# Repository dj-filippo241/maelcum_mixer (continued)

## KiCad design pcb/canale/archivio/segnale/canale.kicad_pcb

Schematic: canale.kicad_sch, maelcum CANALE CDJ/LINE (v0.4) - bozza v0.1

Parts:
C1, C2: 220u 35V; CP_Radial_D8.0mm_P3.50mm
C3: 47u 10V; CP_Radial_D5.0mm_P2.00mm
C4, C8: 10u 35V; CP_Radial_D5.0mm_P2.00mm
C5, C9: 47u 35V; CP_Radial_D6.3mm_P2.50mm
C6, C10: 470u 25V; CP_Radial_D8.0mm_P3.50mm
C7, C11: 100u 25V; CP_Radial_D6.3mm_P2.50mm
C12, C13: 1u 50V; C_1206_3216Metric
C14, C15: 1u 25V; C_1206_3216Metric
C16, C17, C19, C20: 4u7 25V; C_1206_3216Metric
C18, C21: 10u 25V; C_1206_3216Metric
C22: 1u; C_1206_3216Metric
C23, C24, C27, C28, C29, C30, C31, C32, C33, C34, C37, C38, C39, C40, C42, C43, C45, C46, C47, C48, C51, C52, C53, C54, C55, C56, C57, C59, C60, C61, C62, C63: 100n; C_0805_2012Metric
C25, C26: 2u2 film; C_1812_4532Metric
C35: 47p C0G; C_0805_2012Metric
C36: 100n C0G; C_1206_3216Metric
C41, C44: 22p C0G; C_0805_2012Metric
C49, C50: 50n C0G; C_1206_3216Metric
C58: 47n; C_0805_2012Metric
D1, D3, D8, D9, D10, D11, D12, D13: 1N4148W; D_SOD-123
D2, D4: S1G; D_SMA
D5: LM4040-5.0; SOT-23
D6, D7: TVS bidir <=5 pF; D_SOD-323
FB1, FB2, FB3, FB4, FB5, FB6, FB7: ferrite 600R; L_1206_3216Metric
H1, H2: CHASSIS; MountingHole_3.2mm_M3_Pad
J1: C96 maschio; DIN41612_C_3x32_Male_Horizontal_THT
J2: 2x18 cavo piatto; PinHeader_2x18_P2.54mm_Vertical
J3: 1x5 ingressi; PinHeader_1x05_P2.54mm_Vertical
J4: 2x18 ponte isolator; PinHeader_2x18_P2.54mm_Vertical
Q40: BD139; TO-126-3_Vertical
Q41: BD140; TO-126-3_Vertical
R1, R4: 120 1%; R_0805_2012Metric
R2, R5: 1k74 1%; R_0805_2012Metric
R3, R6, R29, R67, R68: 1k; R_0805_2012Metric
R7, R8: 150k 0.1%; R_0805_2012Metric
R9: 1k5; R_0805_2012Metric
R10, R11, R48, R49, R71, R72, R73, R74, R75, R76: 10k 0.1%; R_0805_2012Metric
R12, R17: 100; R_0805_2012Metric
R13, R18, R51, R65, R70: 100k; R_0805_2012Metric
R14, R19: 4k30 0.1%; R_0805_2012Metric
R15, R20: 2k15 0.1%; R_0805_2012Metric
R16, R21, R52: 1k 0.1%; R_0805_2012Metric
R22, R23, R24, R25: 47; R_0805_2012Metric
R26, R27, R31, R35, R36, R40: 20k 0.1%; R_0805_2012Metric
R28: 4k02 0.1%; R_0805_2012Metric
R30: 3M; R_0805_2012Metric
R32, R37: 6k19; R_0805_2012Metric
R33, R38: 150k; R_0805_2012Metric
R34, R39: 51; R_0805_2012Metric
R41: 43.2k 0.1%; R_0805_2012Metric
R42: 68.1k 0.1%; R_0805_2012Metric
R43: 357k 0.1%; R_0805_2012Metric
R44: 20.0k 0.1%; R_0805_2012Metric
R45: 38.3k 0.1%; R_0805_2012Metric
R46: 976 0.1%; R_0805_2012Metric
R47: 1.33k 0.1%; R_0805_2012Metric
R50: 2k 0.1%; R_0805_2012Metric
R53, R55: 1k5 0.1%; R_0805_2012Metric
R54: 909 0.1%; R_0805_2012Metric
R56: 1M5; R_0805_2012Metric
R57, R58, R61, R62, R63, R64, R69: 10k; R_0805_2012Metric
R59, R60: 3k01 0.1%; R_0805_2012Metric
R66: 33k; R_0805_2012Metric
RV1, RV2, RV4: 50k; Potentiometer_Bourns_3266W_Vertical
RV3: 200; Potentiometer_Bourns_3266W_Vertical
U1, U2, U15, U16, U20, U21, U22, U46: OPA1612AIDR; SOIC-8_3.9x4.9mm_P1.27mm
U17: OPA1654AIDR; SOIC-14_3.9x8.7mm_P1.27mm
U18, U19: V2181L; SOIC-8_3.9x4.9mm_P1.27mm
U23: 74HC14PW; TSSOP-14_4.4x5mm_P0.65mm
U24: 74HC86PW; TSSOP-14_4.4x5mm_P0.65mm
U25: 74HC74PW; TSSOP-14_4.4x5mm_P0.65mm
U26, U27: ADG1434YRUZ; TSSOP-20_4.4x6.5mm_P0.65mm
U40: LM317; TO-220-3_Vertical
U41: LM337; TO-220-3_Vertical
U42: 78L15; SOT-89-3
U43: 79L15; SOT-89-3
U44: LT3045EMSE; MSOP-12-1EP_3x4.039mm_P0.65mm_EP1.651x2.845mm
U45: LT3094EMSE; MSOP-12-1EP_3x4.039mm_P0.65mm_EP1.651x2.845mm

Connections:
+5V: FB5.1, J1.a21, J1.a22
+5VF: C3.1, C55.1, C56.1, C57.1, FB5.2, J2.33, R61.1, R63.1, U23.14 (VCC), U24.14 (VCC), U25.1 (1CLR), U25.4 (1PRE), U25.10 (2PRE), U25.13 (2CLR), U25.14 (VCC)
+15LN: C18.1, C23.1, C47.1, C51.1, R9.1, RV1.1, RV2.1, RV4.1, U21.8 (V+), U22.8 (V+), U44.10 (OUTS), U44.11 (OUT), U44.12 (OUT), U46.8 (V+)
+15SW: C14.1, C60.1, C62.1, U26.16 (VDD), U27.16 (VDD), U42.1 (OUT)
+18V: C7.1, C17.1, C27.1, C29.1, C31.1, C33.1, C37.1, C39.1, C42.1, C45.1, J4.1, J4.2, Q40.1 (E), U1.8 (V+), U2.8 (V+), U15.8 (V+), U16.8 (V+), U17.4 (V+), U18.7 (V+), U19.7 (V+), U20.8 (V+), U44.1 (IN), U44.2 (IN), U44.3 (IN), U44.4 (EN/UV), U44.7 (PGFB)
+REF5: J2.26, R10.1, U46.1, U46.2 (-)
-15LN: C21.2, C24.2, C48.2, C52.2, RV1.3, RV2.3, RV4.3, U21.4 (V-), U22.4 (V-), U45.10 (OUTS), U45.11 (OUT), U45.12 (OUT), U46.4 (V-)
-15SW: C15.2, C61.2, C63.2, U26.5 (VSS), U27.5 (VSS), U43.3 (VO)
-18V: C11.2, C20.2, C28.2, C30.2, C32.2, C34.2, C38.2, C40.2, C43.2, C46.2, J4.5, J4.6, Q41.1 (E), R32.2, R37.2, U1.4 (V-), U2.4 (V-), U15.4 (V-), U16.4 (V-), U17.11 (V-), U20.4 (V-), U45.1 (IN), U45.2 (IN), U45.3 (EN/UV), U45.5 (PGFB), U45.13 (IN)
-REF5: R11.2, R43.2, R45.2, R47.2, U46.7
ADJ+: C4.1, D1.2 (A), R1.2, R2.1, U40.1 (ADJ)
ADJ-: C8.2, D3.1 (K), R4.2, R5.1, U41.1 (ADJ)
AGND: C1.2, C2.1, C4.2, C5.2, C6.2, C7.2, C8.1, C9.1, C10.1, C11.1, C12.2, C13.1, C14.2, C15.1, C16.2, C17.2, C18.2, C19.1, C20.1, C21.1, C22.2, C23.2, C24.1, C27.2, C28.1, C29.2, C30.1, C31.2, C32.1, C33.2, C34.1, C36.2, C37.2, C38.1, C39.2, C40.1, C42.2, C43.1, C45.2, C46.1, C47.2, C48.1, C49.2, C50.2, C51.2, C52.1, C60.2, C61.1, C62.2, C63.1, D5.2 (A), D6.2 (A2), D7.2 (A2), J1.a13, J1.a14, J1.a15, J1.a16, J1.a17, J1.a18, J1.a19, J1.a20, J1.b3, J1.b6, J1.b9, J1.b12, J1.b15, J1.b18, J1.b21, J1.b24, J1.b27, J1.b30, J2.1, J2.4, J2.7, J2.16, J2.25, J2.28, J2.35, J2.36, J3.2, J3.4, J4.3, J4.4, J4.7, J4.8, J4.11, J4.12, J4.15, J4.16, J4.25, J4.26, J4.35, J4.36, R2.2, R5.2, R7.2, R8.2, R13.2, R14.2, R16.2, R18.2, R19.2, R21.2, R28.2, R30.2, R34.2, R39.2, R51.2, R53.2, R55.2, U17.12 (+), U18.2 (EC+), U18.6 (GND), U19.2 (EC+), U19.6 (GND), U20.3 (+), U20.5 (+), U21.3 (+), U21.5 (+), U26.4 (S1B), U26.6 (GND), U26.7 (S2B), U26.14 (S3B), U26.17 (S4B), U27.4 (S1B), U27.6 (GND), U27.7 (S2B), U27.14 (S3B), U27.17 (S4B), U42.2 (GND), U43.1 (GND), U44.6 (ILIM), U44.9 (GND), U44.13 (GND), U45.6 (ILIM), U45.9 (GND), U46.5 (+)
BASE+: C6.1, Q40.3 (B), R3.2
BASE-: C10.2, Q41.3 (B), R6.2
BTNC: J2.32, R69.1
BUF_L: J2.2, U1.1, U1.2 (-)
BUF_R: J2.5, U1.6 (-), U1.7
BUS_HPF_L: J1.b10, R72.2
BUS_HPF_R: J1.b11, R75.2
BUS_LPF_L: J1.b13, R73.2
BUS_LPF_R: J1.b14, R76.2
CHASSIS: H1.1, H2.1, J1.a25, J1.a26, J3.5
CLK: U23.8 (4Y), U25.3 (1CLK), U25.11 (2CLK)
CTRL_GND: C3.2, C53.2, C54.2, C55.2, C56.2, C57.2, C58.2, C59.2, J1.a23, J1.a24, J1.c16, J1.c20, J1.c24, J1.c28, J2.34, R65.2, R70.2, U23.7 (GND), U23.13 (6A), U24.7 (GND), U24.12 (4A), U24.13 (4B), U25.7 (GND)
CUEB_L: U15.1, U15.2 (-), U26.19 (S4A)
CUEB_R: U16.1, U16.2 (-), U27.19 (S4A)
CUED_L: R23.1, U26.18 (D4)
CUED_R: R25.1, U27.18 (D4)
CUESEL: C59.1, R69.2, R70.1, U26.20 (IN4), U27.20 (IN4)
CUE_OUT_L: J1.b4, R23.2
CUE_OUT_R: J1.b5, R25.2
CVP_F: R50.2, R52.1, R54.1, U21.7
D0: U23.2 (1Y), U24.1 (1A), U25.2 (1D)
D1: U23.4 (2Y), U24.4 (2A), U25.12 (2D)
D1A: D8.2 (A), R29.2
DIFF: D12.1 (K), D13.1 (K), R57.1, R65.1, R66.1
DIPCV: R59.1, R60.1, U22.6 (-), U22.7
DJBUS_L: J1.b1, R71.2
DJBUS_R: J1.b2, R74.2
DJD_L: R71.1, U26.3 (D1)
DJD_R: R74.1, U27.3 (D1)
DJSEL: U23.10 (5Y), U26.1 (IN1), U27.1 (IN1)
DLY: C58.1, R66.2, U23.5 (3A)
DOUT: C35.1, R29.1, U17.7
DP1: C49.1, R57.2, U22.3 (+)
DP2: C50.1, R58.2, U22.5 (+)
DPB1: R58.1, U22.1, U22.2 (-)
ECF_L: R52.2, R53.1, R59.2, U18.3 (EC-)
ECF_R: R55.1, R56.2, R60.2, RV3.2, RV3.3, U19.3 (EC-)
EQ_L: J4.13, R26.1, R31.1, U15.3 (+), U15.5 (+)
EQ_R: J4.14, R27.1, R36.1, U16.3 (+), U16.5 (+)
FAD_L: C41.2, R35.2, U20.1, U26.2 (S1A), U26.9 (S2A), U26.12 (S3A)
FAD_R: C44.2, R40.2, U20.7, U27.2 (S1A), U27.9 (S2A), U27.12 (S3A)
FILT_MODE1_0: J1.c1, R67.2
FILT_MODE1_1: J1.c2, R68.2
FR0: C53.1, R62.2, U23.1 (1A)
FR1: C54.1, R64.2, U23.3 (2A)
FSW0: J2.30, R61.2, R62.1
FSW1: J2.31, R63.2, R64.1
GO_L: J4.9, R15.1, U2.1
GO_R: J4.10, R20.1, U2.7
GW_L: J2.3, R14.1, U2.3 (+)
GW_R: J2.6, R19.1, U2.5 (+)
HIO_L: J2.14, J4.23
HIO_R: J2.23, J4.33
HOLD: C35.2, C36.1, D8.1 (K), R30.1, U17.6 (-), U17.10 (+)
HPD_L: R72.1, U26.8 (D2)
HPD_R: R75.1, U27.8 (D2)
INC_L: C25.2, R13.1, U1.3 (+)
INC_R: C26.2, R18.1, U1.5 (+)
INF_L: FB6.2, R12.1
INF_R: FB7.2, R17.1
INP_L: C25.1, D6.1 (A1), R12.2
INP_R: C26.1, D7.1 (A1), R17.2
IN_L: FB6.1, J3.1
IN_R: FB7.1, J3.3
K1W_L: J2.9, J4.18
K1W_R: J2.18, J4.28
K2W_L: J2.11, J4.20
K2W_R: J2.20, J4.30
K3W_L: J2.13, J4.22
K3W_R: J2.22, J4.32
K4W_L: J2.15, J4.24
K4W_R: J2.24, J4.34
LMO_L: J2.10, J4.19
LMO_R: J2.19, J4.29
LOO_L: J2.8, J4.17
LOO_R: J2.17, J4.27
LPD_L: R73.1, U26.13 (D3)
LPD_R: R76.1, U27.13 (D3)
LT_F: R54.2, RV3.1
MET: J2.29, U17.8, U17.9 (-)
MG: R26.2, R27.2, R28.1, U17.3 (+)
MGB: U17.1, U17.2 (-), U17.5 (+)
MHO_L: J2.12, J4.21
MHO_R: J2.21, J4.31
NCLK: U23.6 (3Y), U23.9 (4A)
NG_L: R15.2, R16.1, U2.2 (-)
NG_R: R20.2, R21.1, U2.6 (-)
NIF_L: C41.1, R35.1, U18.8 (OUT), U20.2 (-)
NIF_R: C44.1, R40.1, U19.8 (OUT), U20.6 (-)
NP_F: R49.2, R50.1, U21.6 (-)
NREF5I: R10.2, R11.1, U46.6 (-)
NU17: U17.13 (-), U17.14
OF_F: R56.1, RV4.2
POT_F: J2.27, R41.1, R42.1, R44.1, R46.1, R51.1
Q0: R67.1, U24.2 (1B), U24.9 (3A), U25.5 (1Q), U26.10 (IN2), U27.10 (IN2)
Q1: R68.1, U24.5 (2B), U24.10 (3B), U25.9 (2Q), U26.11 (IN3), U27.11 (IN3)
RAW+22: FB3.1, J1.a5, J1.a6
RAW+27: FB1.1, J1.a1, J1.a2
RAW-22: FB4.1, J1.a7, J1.a8
RAW-27: FB2.1, J1.a3, J1.a4
REF5K: C22.1, D5.1 (K), R9.2, U46.3 (+)
SEND_TAP_L: J1.b7, R22.2
SEND_TAP_R: J1.b8, R24.2
SETN: C19.2, R8.1, U45.8 (SET)
SETP: C16.1, R7.1, U44.8 (SET)
SH_F: R48.2, R49.1, U21.1
SJ_F: D9.1 (K), D10.1 (K), D11.1 (K), R41.2, R48.1, U21.2 (-)
SN1_F: D9.2 (A), R42.2, R43.1
SN2_F: D10.2 (A), R44.2, R45.1
SN3_F: D11.2 (A), R46.2, R47.1
STB_L: R22.1, U15.6 (-), U15.7
STB_R: R24.1, U16.6 (-), U16.7
SW_fl: R33.1, RV1.2
SW_fr: R38.1, RV2.2
SYM_fl: R33.2, R34.1, U18.4 (SYM)
SYM_fr: R38.2, R39.1, U19.4 (SYM)
V22F+: C12.1, FB3.2, U42.3 (IN)
V22F-: C13.2, FB4.2, U43.2 (VI)
V27F+: C1.1, D2.1 (K), FB1.2, U40.3 (VI)
V27F-: C2.2, D4.2 (A), FB2.2, U41.2 (VI)
VEE_fl: R32.1, U18.5 (V-)
VEE_fr: R37.1, U19.5 (V-)
VIN_fl: R31.2, U18.1 (IN)
VIN_fr: R36.2, U19.1 (IN)
VREG+: C5.1, D1.1 (K), D2.2 (A), Q40.2 (C), R1.1, R3.1, U40.2 (VO)
VREG-: C9.2, D3.2 (A), D4.1 (K), Q41.2 (C), R4.1, R6.1, U41.3 (VO)
X0: D12.2 (A), U24.3 (1Y)
X1: D13.2 (A), U24.6 (2Y)
XQ: U23.11 (5A), U24.8 (3Y)

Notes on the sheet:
BACKPLANE C96 (classe CDJ, REV dec. 159)
ALIMENTAZIONE +-18 audio, +-15 switch, +5, +-15 LN, +-5 riferimento
INGRESSO LINE [A] e GAIN T1 [B] (dec. 162)
PONTE verso la scheda ISOLATOR (J4)
CUE [D], SEND TAP [E] e METER [G] (pre-fader)
FADER [H] (2 VCA, shaper del fader, dec. 126) e DIP (dec. 163)
LEVETTA HPF/OFF/LPF: logica autotemporizzata (74HC14, 74HC86, 74HC74) e ADG1434
CAVO SCHEDA COMANDI (J2) e INGRESSI RCA (J3)

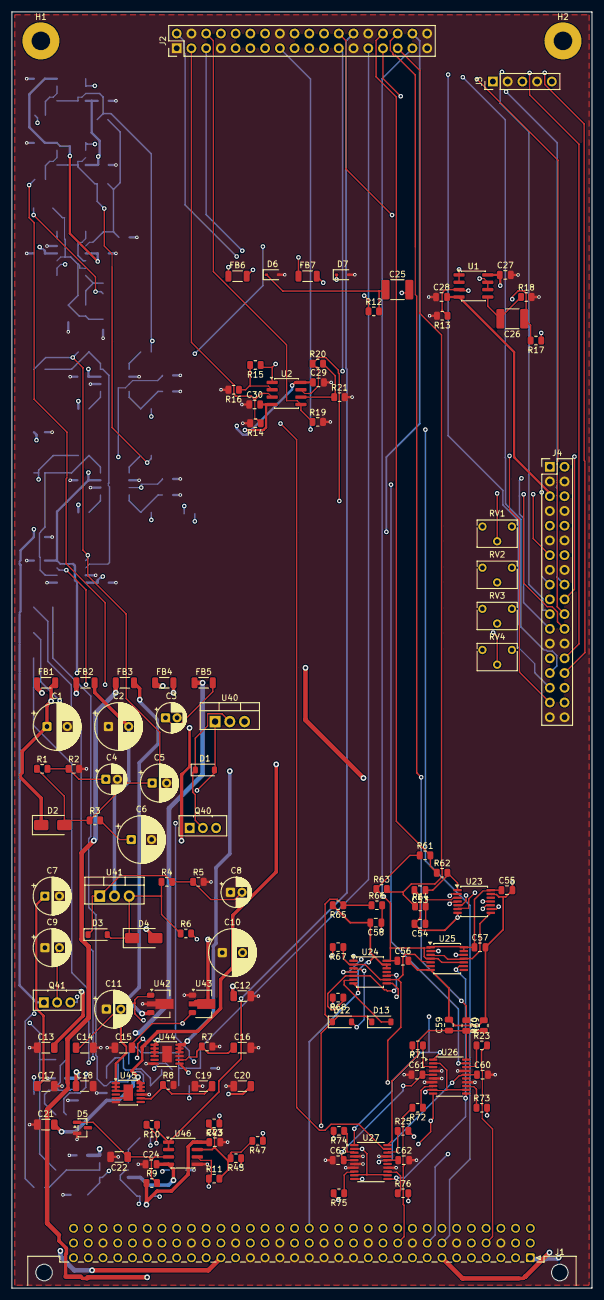
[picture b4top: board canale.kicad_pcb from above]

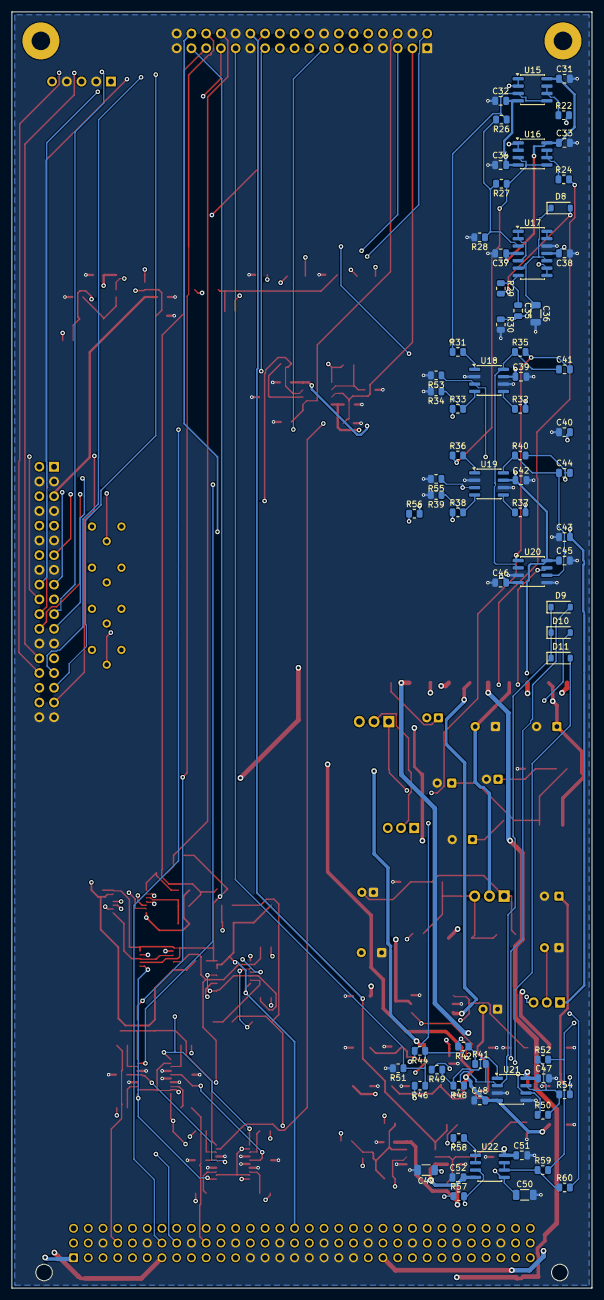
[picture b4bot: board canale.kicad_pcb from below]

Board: 4 copper layers, 100.0 x 220.0 mm, 193 parts (68 on the bottom side), 142 nets.

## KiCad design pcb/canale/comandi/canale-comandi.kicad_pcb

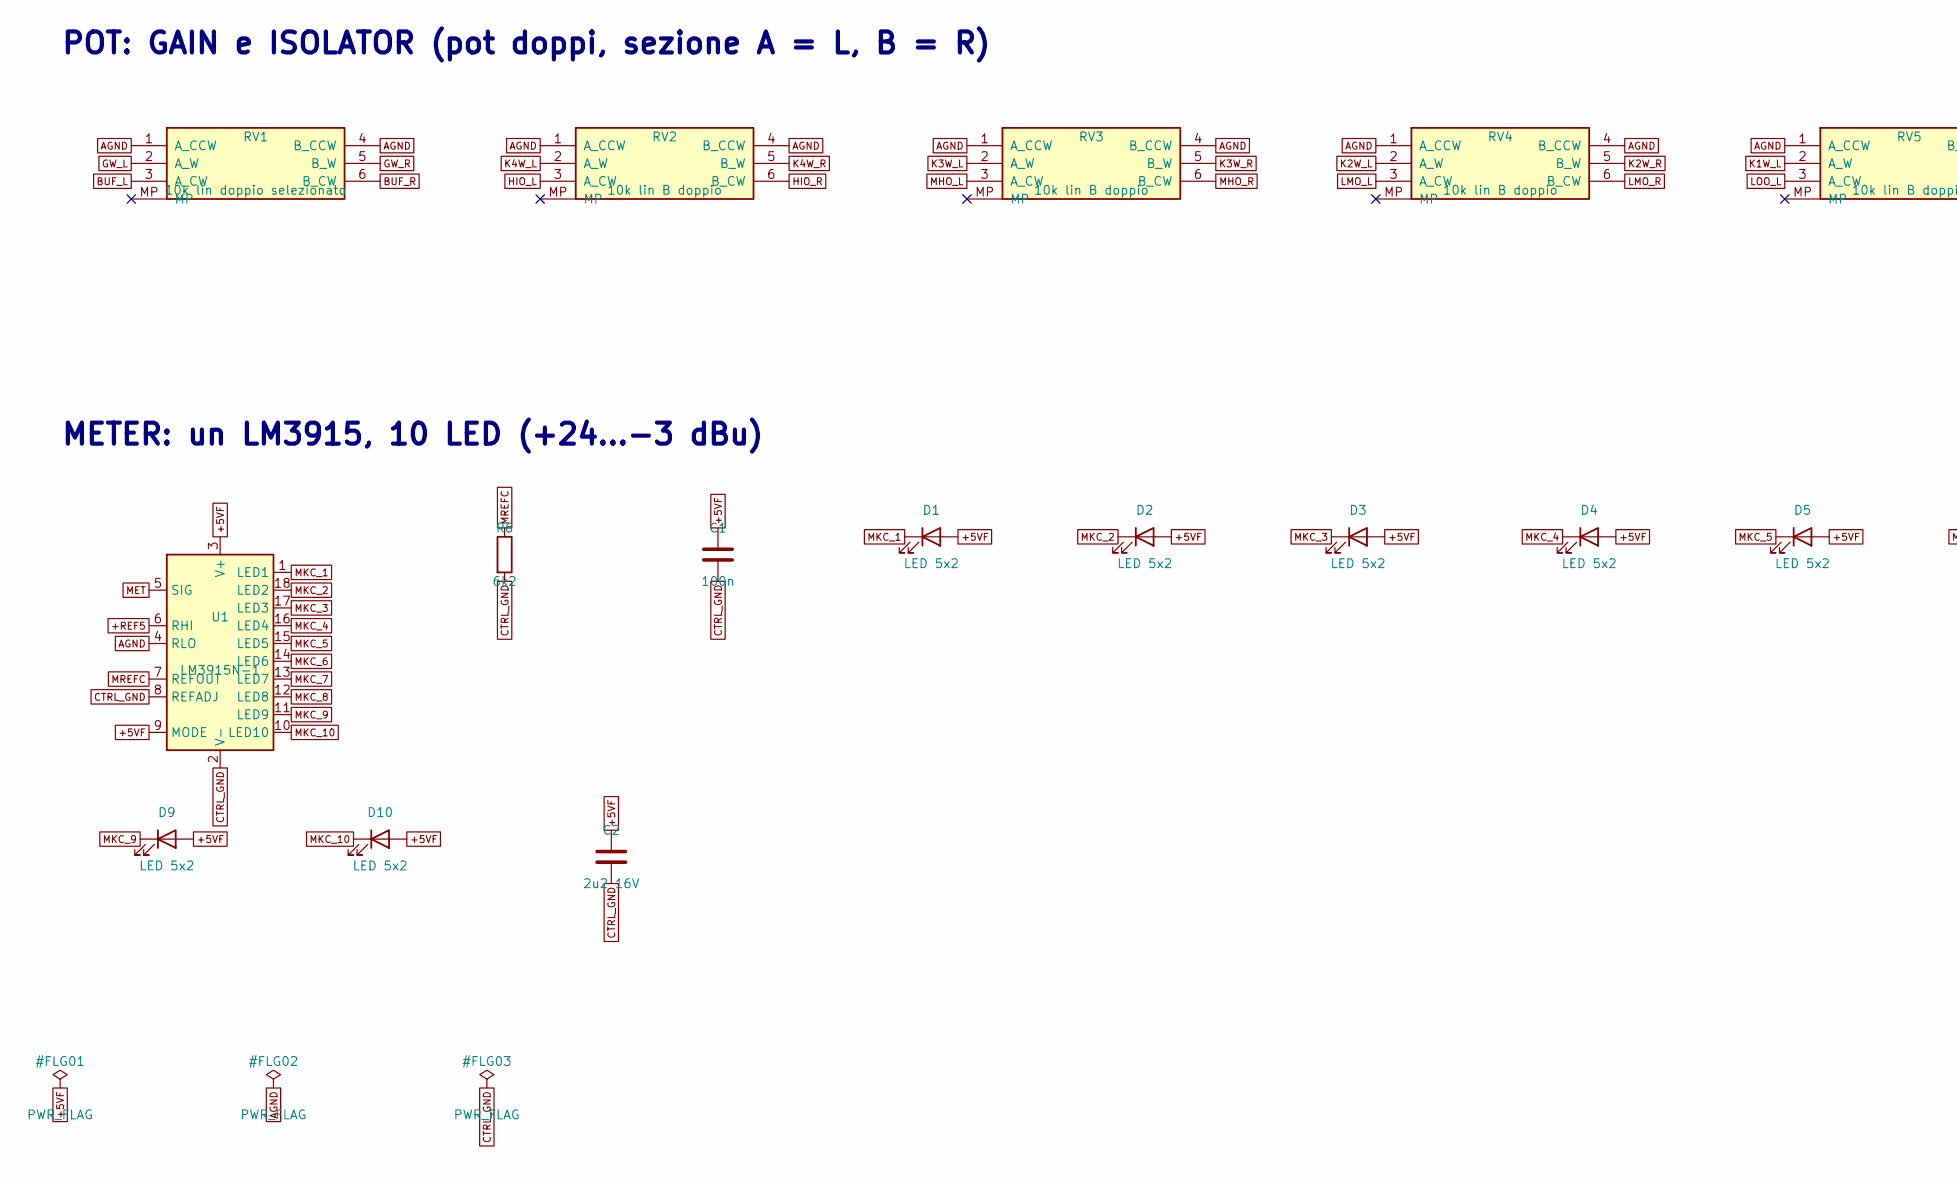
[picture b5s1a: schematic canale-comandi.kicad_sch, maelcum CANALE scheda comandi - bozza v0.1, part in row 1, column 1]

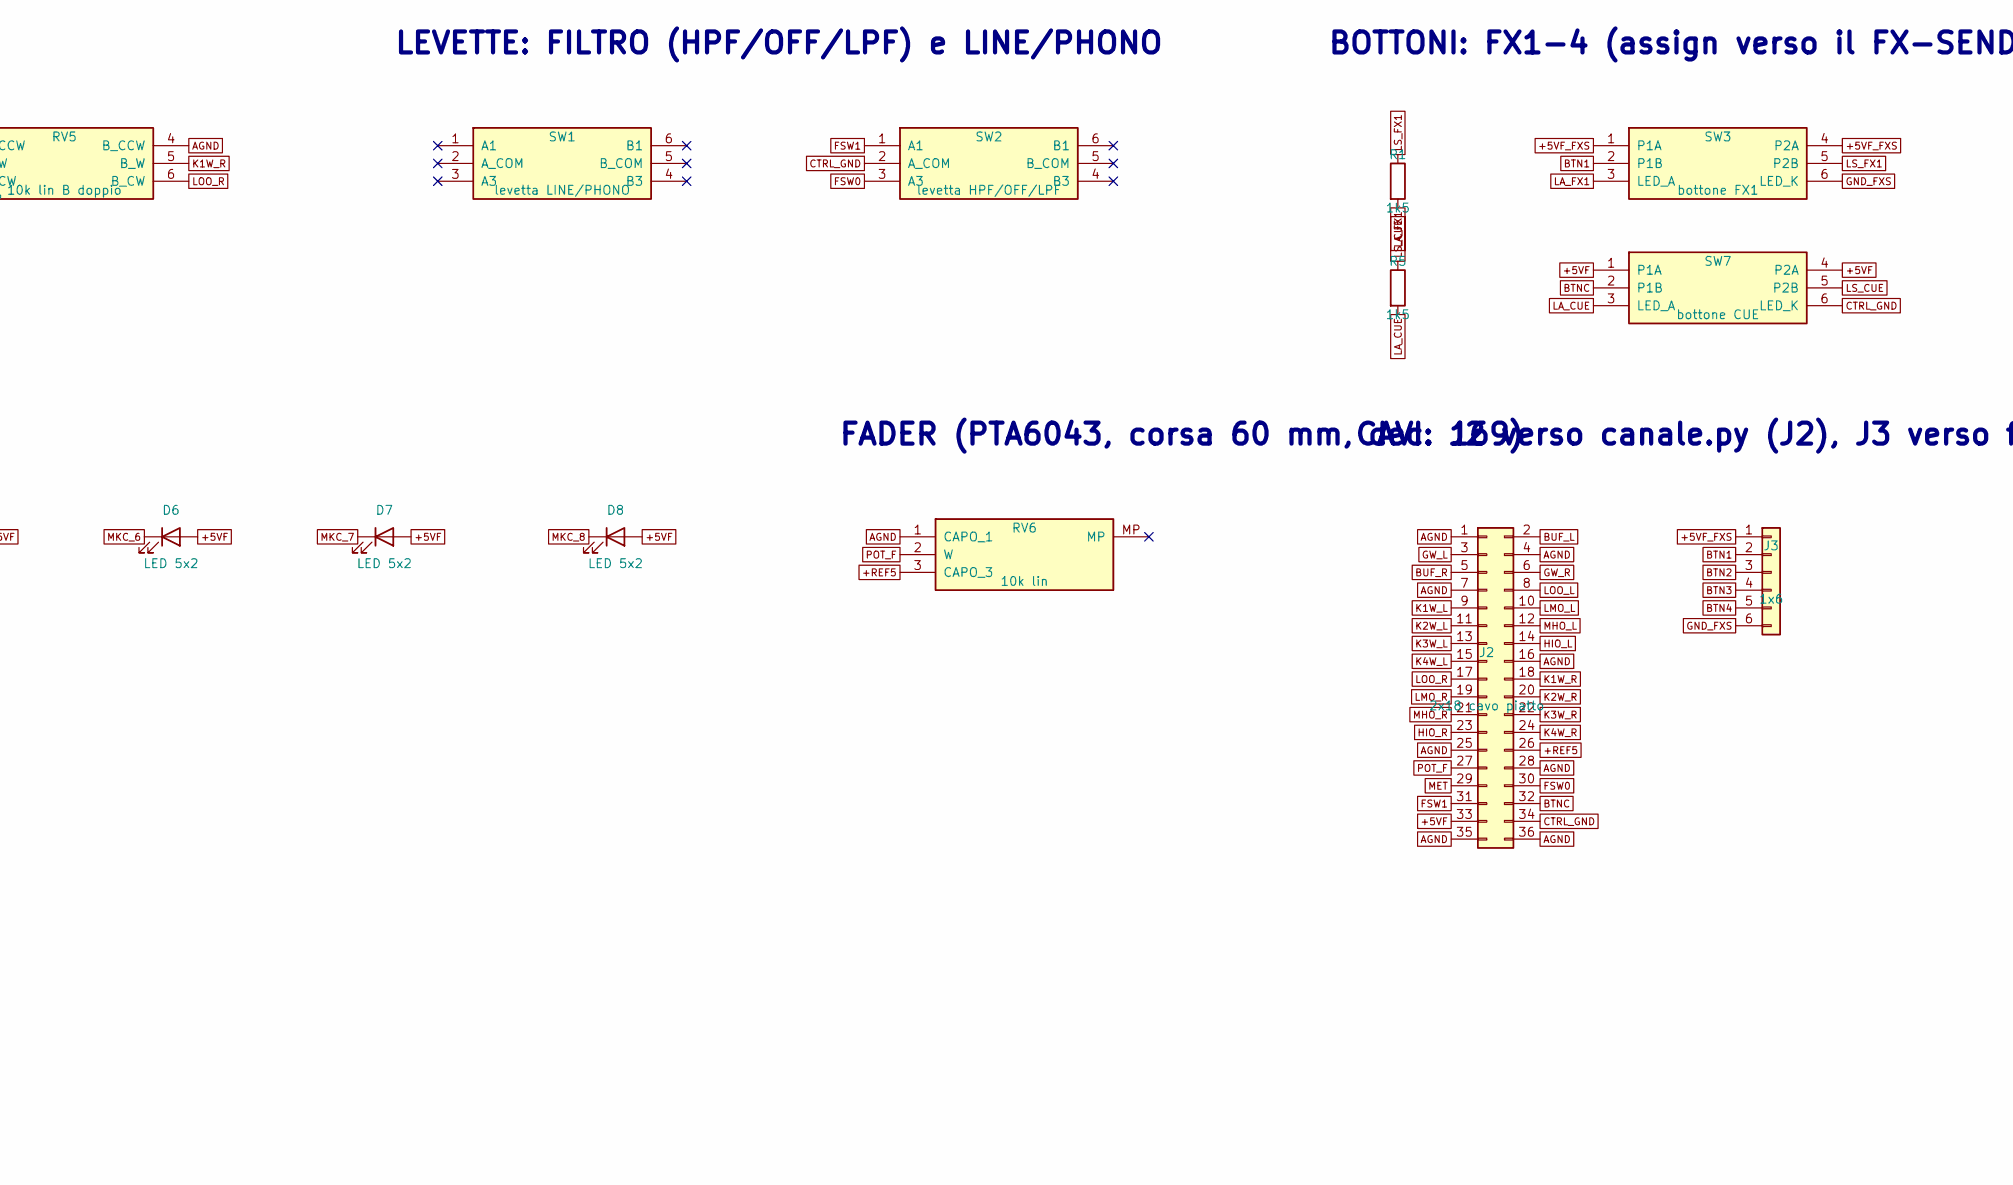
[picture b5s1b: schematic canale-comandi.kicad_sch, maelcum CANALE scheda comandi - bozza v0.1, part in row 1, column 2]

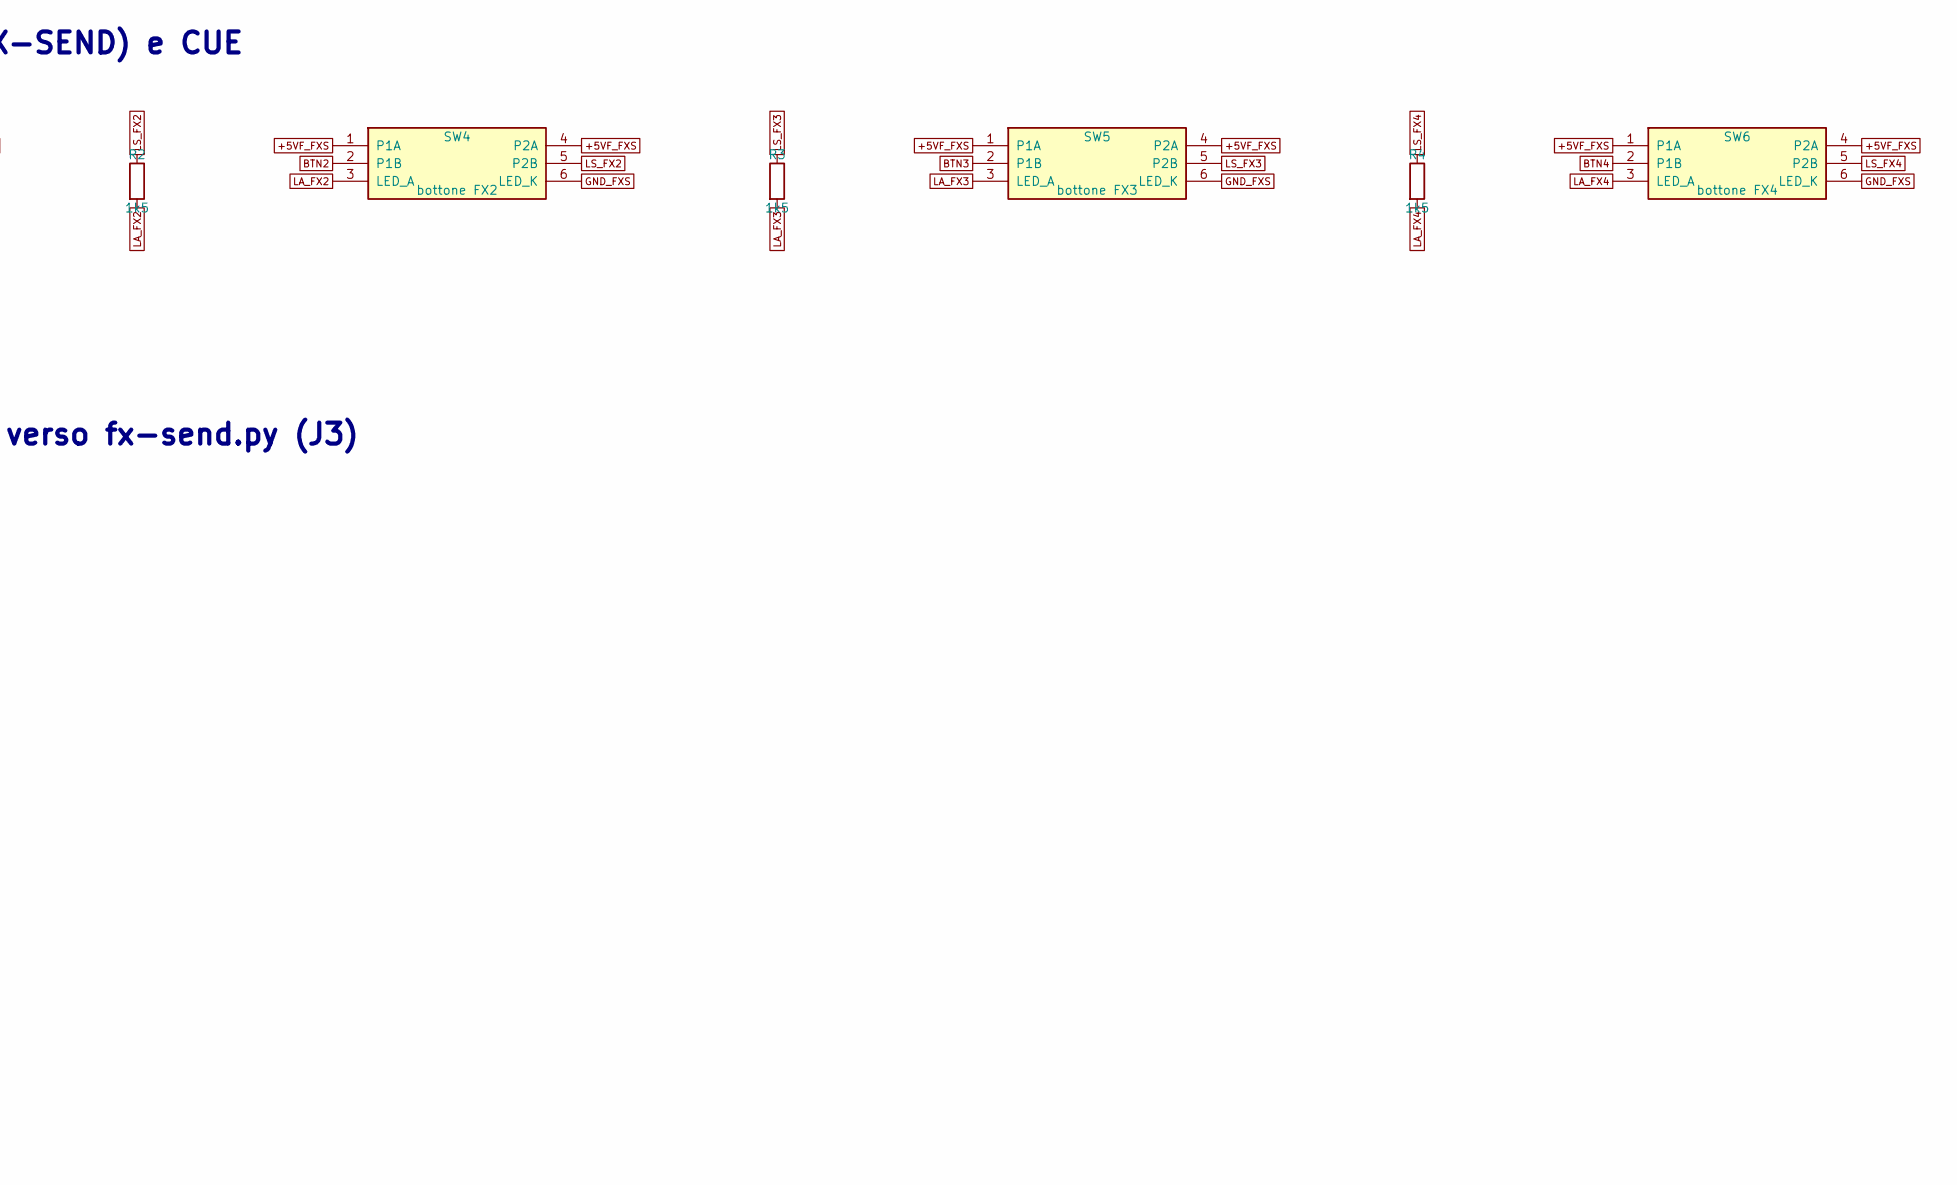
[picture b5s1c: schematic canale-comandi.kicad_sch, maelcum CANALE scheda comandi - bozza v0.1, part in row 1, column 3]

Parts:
C1: 100n; C_0805_2012Metric
C2: 2u2 16V; C_1206_3216Metric
D1, D2, D3, D4, D5, D6, D7, D8, D9, D10: LED 5x2; LED_Rectangular_W5.0mm_H2.0mm
J2: 2x18 cavo piatto; PinHeader_2x18_P2.54mm_Vertical
J3: 1x6; PinHeader_1x06_P2.54mm_Vertical
R1, R2, R3, R4, R5: 1k5; R_0805_2012Metric
R6: 6k2; R_0805_2012Metric
RV1: 10k lin doppio selezionato; Potentiometer_Alps_RK09L_Double_Vertical
RV2, RV3, RV4, RV5: 10k lin B doppio; Potentiometer_Alps_RK09L_Double_Vertical
RV6: 10k lin; Potentiometer_Bourns_PTA6043_Single_Slide
SW1: levetta LINE/PHONO; SW_NKK_G1xJP
SW2: levetta HPF/OFF/LPF; SW_NKK_G1xJP
SW3: bottone FX1; SW_NKK_GW12LJP
SW4: bottone FX2; SW_NKK_GW12LJP
SW5: bottone FX3; SW_NKK_GW12LJP
SW6: bottone FX4; SW_NKK_GW12LJP
SW7: bottone CUE; SW_NKK_GW12LJP
U1: LM3915N-1; DIP-18_W7.62mm

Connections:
+5VF: C1.1, C2.1, D1.2 (A), D2.2 (A), D3.2 (A), D4.2 (A), D5.2 (A), D6.2 (A), D7.2 (A), D8.2 (A), D9.2 (A), D10.2 (A), J2.33, SW7.1 (P1A), SW7.4 (P2A), U1.3 (V+), U1.9 (MODE)
+5VF_FXS: J3.1, SW3.1 (P1A), SW3.4 (P2A), SW4.1 (P1A), SW4.4 (P2A), SW5.1 (P1A), SW5.4 (P2A), SW6.1 (P1A), SW6.4 (P2A)
+REF5: J2.26, RV6.3 (CAPO_3), U1.6 (RHI)
AGND: J2.1, J2.4, J2.7, J2.16, J2.25, J2.28, J2.35, J2.36, RV1.1 (A_CCW), RV1.4 (B_CCW), RV2.1 (A_CCW), RV2.4 (B_CCW), RV3.1 (A_CCW), RV3.4 (B_CCW), RV4.1 (A_CCW), RV4.4 (B_CCW), RV5.1 (A_CCW), RV5.4 (B_CCW), RV6.1 (CAPO_1), U1.4 (RLO)
BTN1: J3.2, SW3.2 (P1B)
BTN2: J3.3, SW4.2 (P1B)
BTN3: J3.4, SW5.2 (P1B)
BTN4: J3.5, SW6.2 (P1B)
BTNC: J2.32, SW7.2 (P1B)
BUF_L: J2.2, RV1.3 (A_CW)
BUF_R: J2.5, RV1.6 (B_CW)
CTRL_GND: C1.2, C2.2, J2.34, R6.2, SW2.2 (A_COM), SW7.6 (LED_K), U1.2 (V-), U1.8 (REFADJ)
FSW0: J2.30, SW2.3 (A3)
FSW1: J2.31, SW2.1 (A1)
GND_FXS: J3.6, SW3.6 (LED_K), SW4.6 (LED_K), SW5.6 (LED_K), SW6.6 (LED_K)
GW_L: J2.3, RV1.2 (A_W)
GW_R: J2.6, RV1.5 (B_W)
HIO_L: J2.14, RV2.3 (A_CW)
HIO_R: J2.23, RV2.6 (B_CW)
K1W_L: J2.9, RV5.2 (A_W)
K1W_R: J2.18, RV5.5 (B_W)
K2W_L: J2.11, RV4.2 (A_W)
K2W_R: J2.20, RV4.5 (B_W)
K3W_L: J2.13, RV3.2 (A_W)
K3W_R: J2.22, RV3.5 (B_W)
K4W_L: J2.15, RV2.2 (A_W)
K4W_R: J2.24, RV2.5 (B_W)
LA_CUE: R5.2, SW7.3 (LED_A)
LA_FX1: R1.2, SW3.3 (LED_A)
LA_FX2: R2.2, SW4.3 (LED_A)
LA_FX3: R3.2, SW5.3 (LED_A)
LA_FX4: R4.2, SW6.3 (LED_A)
LMO_L: J2.10, RV4.3 (A_CW)
LMO_R: J2.19, RV4.6 (B_CW)
LOO_L: J2.8, RV5.3 (A_CW)
LOO_R: J2.17, RV5.6 (B_CW)
LS_CUE: R5.1, SW7.5 (P2B)
LS_FX1: R1.1, SW3.5 (P2B)
LS_FX2: R2.1, SW4.5 (P2B)
LS_FX3: R3.1, SW5.5 (P2B)
LS_FX4: R4.1, SW6.5 (P2B)
MET: J2.29, U1.5 (SIG)
MHO_L: J2.12, RV3.3 (A_CW)
MHO_R: J2.21, RV3.6 (B_CW)
MKC_1: D1.1 (K), U1.1 (LED1)
MKC_2: D2.1 (K), U1.18 (LED2)
MKC_3: D3.1 (K), U1.17 (LED3)
MKC_4: D4.1 (K), U1.16 (LED4)
MKC_5: D5.1 (K), U1.15 (LED5)
MKC_6: D6.1 (K), U1.14 (LED6)
MKC_7: D7.1 (K), U1.13 (LED7)
MKC_8: D8.1 (K), U1.12 (LED8)
MKC_9: D9.1 (K), U1.11 (LED9)
MKC_10: D10.1 (K), U1.10 (LED10)
MREFC: R6.1, U1.7 (REFOUT)
POT_F: J2.27, RV6.2 (W)

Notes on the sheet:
POT: GAIN e ISOLATOR (pot doppi, sezione A = L, B = R)
LEVETTE: FILTRO (HPF/OFF/LPF) e LINE/PHONO
BOTTONI: FX1-4 (assign verso il FX-SEND) e CUE
METER: un LM3915, 10 LED (+24...-3 dBu)
FADER (PTA6043, corsa 60 mm, dec. 169)
CAVI: J2 verso canale.py (J2), J3 verso fx-send.py (J3)

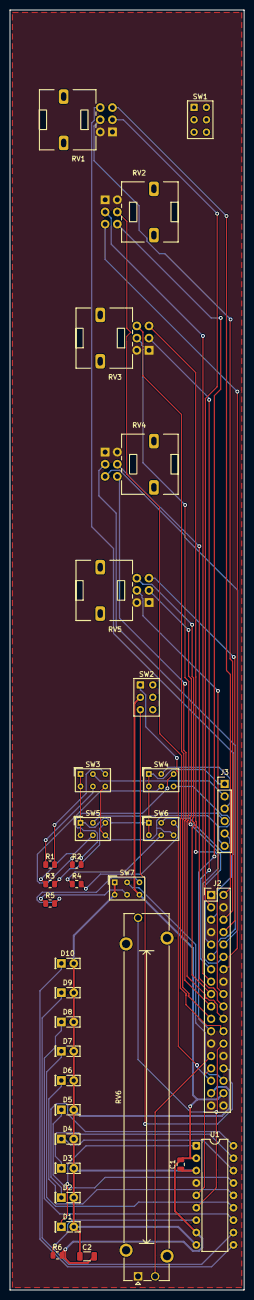
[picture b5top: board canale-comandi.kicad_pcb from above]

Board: 4 copper layers, 48.0 x 262.4 mm, 34 parts (0 on the bottom side), 56 nets.

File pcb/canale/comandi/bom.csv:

quantita;valore;impronta;riferimenti;nota
1;100n;C_0805_2012Metric;C1;disaccoppiamento dell'LM3915 C
1;2u2 16V;C_1206_3216Metric;C2;NOTA: riserva locale dei LED (cavo lungo)
1;LED 5x2;LED_Rectangular_W5.0mm_H2.0mm;D1;barra METER, segmento 1 di 10 (1 = soglia più bassa); colore: metering §3
1;LED 5x2;LED_Rectangular_W5.0mm_H2.0mm;D10;barra METER, segmento 10 di 10 (1 = soglia più bassa); colore: metering §3
1;LED 5x2;LED_Rectangular_W5.0mm_H2.0mm;D2;barra METER, segmento 2 di 10 (1 = soglia più bassa); colore: metering §3
1;LED 5x2;LED_Rectangular_W5.0mm_H2.0mm;D3;barra METER, segmento 3 di 10 (1 = soglia più bassa); colore: metering §3
1;LED 5x2;LED_Rectangular_W5.0mm_H2.0mm;D4;barra METER, segmento 4 di 10 (1 = soglia più bassa); colore: metering §3
1;LED 5x2;LED_Rectangular_W5.0mm_H2.0mm;D5;barra METER, segmento 5 di 10 (1 = soglia più bassa); colore: metering §3
1;LED 5x2;LED_Rectangular_W5.0mm_H2.0mm;D6;barra METER, segmento 6 di 10 (1 = soglia più bassa); colore: metering §3
1;LED 5x2;LED_Rectangular_W5.0mm_H2.0mm;D7;barra METER, segmento 7 di 10 (1 = soglia più bassa); colore: metering §3
1;LED 5x2;LED_Rectangular_W5.0mm_H2.0mm;D8;barra METER, segmento 8 di 10 (1 = soglia più bassa); colore: metering §3
1;LED 5x2;LED_Rectangular_W5.0mm_H2.0mm;D9;barra METER, segmento 9 di 10 (1 = soglia più bassa); colore: metering §3
1;2x18 cavo piatto;PinHeader_2x18_P2.54mm_Vertical;J2;stesso ordine di J2 su canale.py
1;1x6;PinHeader_1x06_P2.54mm_Vertical;J3;stesso ordine di J3 su fx-send.py: +5VF, BTN1-4, CTRL_GND (bottoni assign, dec. 133)
1;1k5;R_0805_2012Metric;R1;luce del bottone FX1 dal secondo contatto
1;1k5;R_0805_2012Metric;R2;luce del bottone FX2 dal secondo contatto
1;1k5;R_0805_2012Metric;R3;luce del bottone FX3 dal secondo contatto
1;1k5;R_0805_2012Metric;R4;luce del bottone FX4 dal secondo contatto
1;1k5;R_0805_2012Metric;R5;luce del bottone CUE dal secondo contatto
1;6k2;R_0805_2012Metric;R6;NOTA: corrente dei LED ~2 mA (metering §1): I = 12,5 V / R, formula del datasheet LM3915 da verificare
1;10k lin doppio selezionato;Potentiometer_Alps_RK09L_Double_Vertical;RV1;GAIN T1 (dec. 162): antiorario = silenzio; pot selezionato per il tracking L/R; manopola GAIN, pot di classe 9 mm, cappuccio 11.0 mm
1;10k lin B doppio;Potentiometer_Alps_RK09L_Double_Vertical;RV2;ISOLATOR HIGH (dec. 168): antiorario = kill, orario = banda piena; manopola HIGH, pot di classe 14 mm, cappuccio 15.0 mm
1;10k lin B doppio;Potentiometer_Alps_RK09L_Double_Vertical;RV3;ISOLATOR MID-HIGH (dec. 168): antiorario = kill, orario = banda piena; manopola MID-HIGH, pot di classe 14 mm, cappuccio 15.0 mm
1;10k lin B doppio;Potentiometer_Alps_RK09L_Double_Vertical;RV4;ISOLATOR LOW-MID (dec. 168): antiorario = kill, orario = banda piena; manopola LOW-MID, pot di classe 14 mm, cappuccio 15.0 mm
1;10k lin B doppio;Potentiometer_Alps_RK09L_Double_Vertical;RV5;ISOLATOR LOW (dec. 168): antiorario = kill, orario = banda piena; manopola LOW, pot di classe 14 mm, cappuccio 15.0 mm
1;10k lin;Potentiometer_Bourns_PTA6043_Single_Slide;RV6;FADER: in cima = 0 dB (Vx = 5 V), in fondo = silenzio; fader FADER, corsa 60 mm (Bourns PTA6043, NOTA: pezzo da confermare)
1;levetta LINE/PHONO;SW_NKK_G1xJP;SW1;LINE/PHONO senza reti: il PHONO arriva con la Rev B (NOTE.md punto 8); levetta LINE/PHONO; NOTA: impronta segnaposto (NKK G1xJP)
1;levetta HPF/OFF/LPF;SW_NKK_G1xJP;SW2;HPF = FSW0 a massa, OFF = nessuno, LPF = FSW1 a massa (dec. 163); levetta FILTRO; NOTA: impronta segnaposto (NKK G1xJP)
1;bottone FX1;SW_NKK_GW12LJP;SW3;FX1: chiuso = +5VF del FX-SEND su BTN1; luce dal secondo contatto; bottone FX1 a ritenuta con luce; NOTA: impronta segnaposto (NKK GW12LJP)
1;bottone FX2;SW_NKK_GW12LJP;SW4;FX2: chiuso = +5VF del FX-SEND su BTN2; luce dal secondo contatto; bottone FX2 a ritenuta con luce; NOTA: impronta segnaposto (NKK GW12LJP)
1;bottone FX3;SW_NKK_GW12LJP;SW5;FX3: chiuso = +5VF del FX-SEND su BTN3; luce dal secondo contatto; bottone FX3 a ritenuta con luce; NOTA: impronta segnaposto (NKK GW12LJP)
1;bottone FX4;SW_NKK_GW12LJP;SW6;FX4: chiuso = +5VF del FX-SEND su BTN4; luce dal secondo contatto; bottone FX4 a ritenuta con luce; NOTA: impronta segnaposto (NKK GW12LJP)
1;bottone CUE;SW_NKK_GW12LJP;SW7;CUE: chiuso = +5VF su BTNC; luce ~2 mA dal secondo contatto; bottone CUE a ritenuta con luce; NOTA: impronta segnaposto (NKK GW12LJP)
1;LM3915N-1;DIP-18_W7.62mm;U1;barra METER, 10 segmenti da 3 dB sotto +REF5; modo barra (MODE a V+); V- a CTRL_GND: le correnti dei LED restano fuori da AGND

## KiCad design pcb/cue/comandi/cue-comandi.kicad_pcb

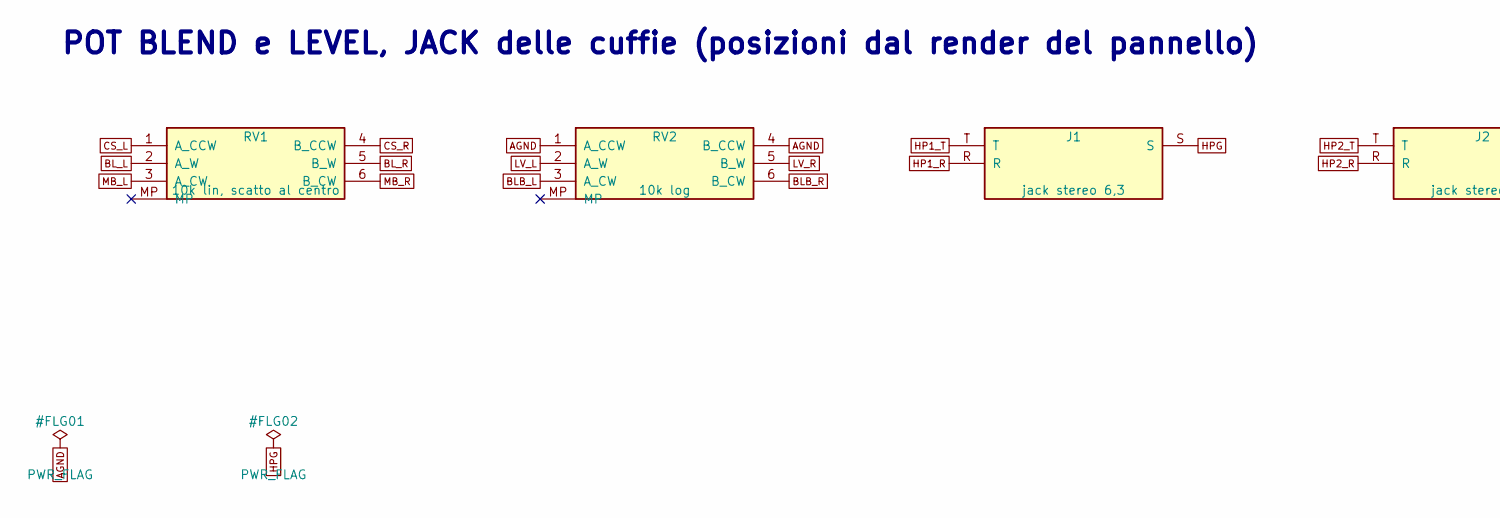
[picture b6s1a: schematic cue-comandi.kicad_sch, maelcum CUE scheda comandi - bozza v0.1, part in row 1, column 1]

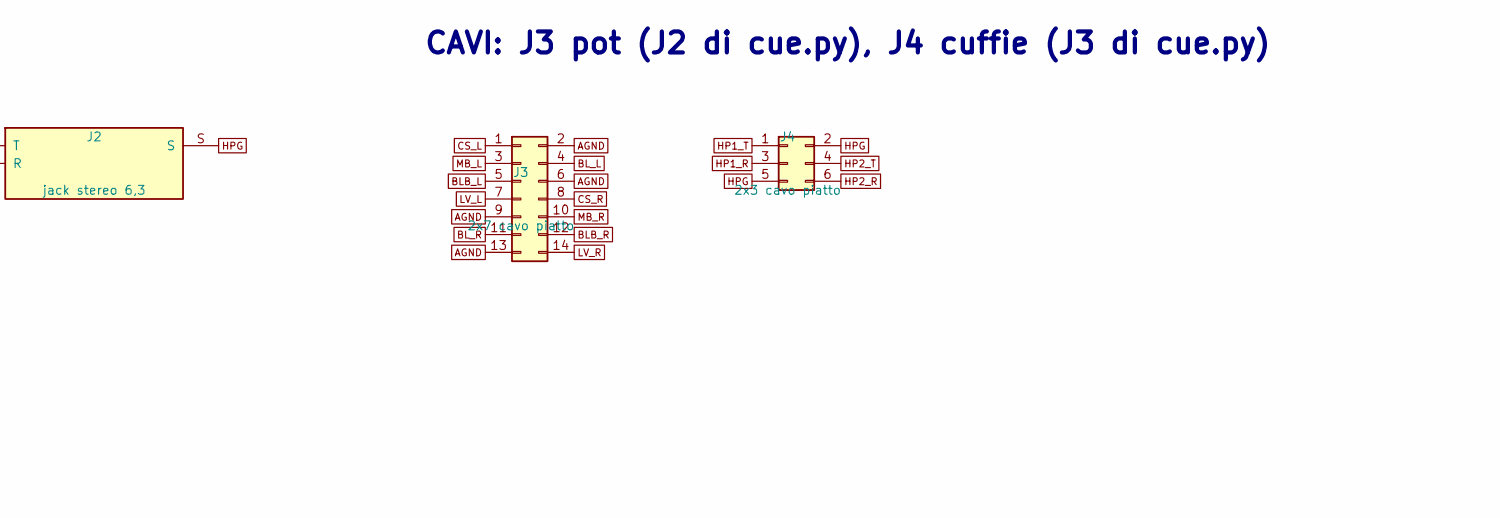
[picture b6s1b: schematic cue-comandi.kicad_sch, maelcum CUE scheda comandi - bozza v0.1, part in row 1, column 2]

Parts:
J1, J2: jack stereo 6,3; Jack_6.35mm_Neutrik_NJ3FD-V_Vertical
J3: 2x7 cavo piatto; PinHeader_2x07_P2.54mm_Vertical
J4: 2x3 cavo piatto; PinHeader_2x03_P2.54mm_Vertical
RV1: 10k lin, scatto al centro; Potentiometer_Alps_RK09L_Double_Vertical
RV2: 10k log; Potentiometer_Alps_RK09L_Double_Vertical

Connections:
AGND: J3.2, J3.6, J3.9, J3.13, RV2.1 (A_CCW), RV2.4 (B_CCW)
BLB_L: J3.5, RV2.3 (A_CW)
BLB_R: J3.12, RV2.6 (B_CW)
BL_L: J3.4, RV1.2 (A_W)
BL_R: J3.11, RV1.5 (B_W)
CS_L: J3.1, RV1.1 (A_CCW)
CS_R: J3.8, RV1.4 (B_CCW)
HP1_R: J1.R, J4.3
HP1_T: J1.T, J4.1
HP2_R: J2.R, J4.6
HP2_T: J2.T, J4.4
HPG: J1.S, J2.S, J4.2, J4.5
LV_L: J3.7, RV2.2 (A_W)
LV_R: J3.14, RV2.5 (B_W)
MB_L: J3.3, RV1.3 (A_CW)
MB_R: J3.10, RV1.6 (B_CW)

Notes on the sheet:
POT BLEND e LEVEL, JACK delle cuffie (posizioni dal render del pannello)
CAVI: J3 pot (J2 di cue.py), J4 cuffie (J3 di cue.py)

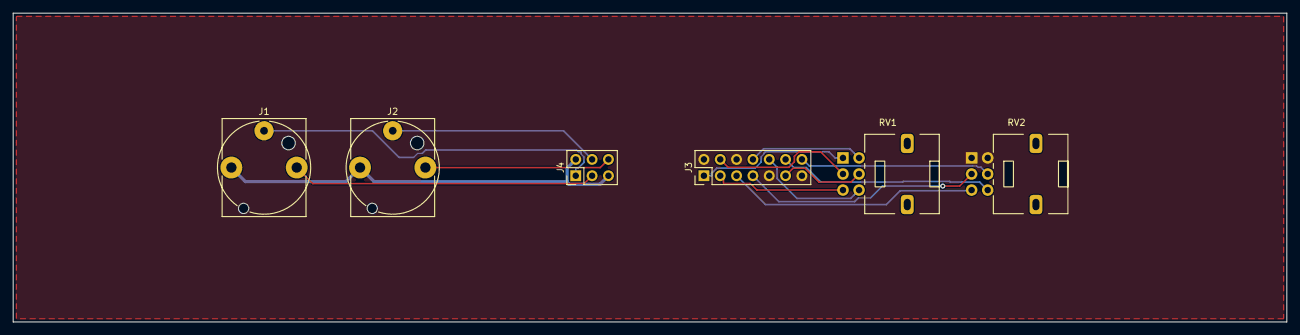
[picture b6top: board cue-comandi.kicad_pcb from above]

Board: 4 copper layers, 198.0 x 48.0 mm, 6 parts (0 on the bottom side), 16 nets.

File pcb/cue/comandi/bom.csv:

quantita;valore;impronta;riferimenti;nota
1;jack stereo 6,3;Jack_6.35mm_Neutrik_NJ3FD-V_Vertical;J1;punta L, anello R, manicotto HPG; PHONES 1 (dec. 128)
1;jack stereo 6,3;Jack_6.35mm_Neutrik_NJ3FD-V_Vertical;J2;punta L, anello R, manicotto HPG; PHONES 2 (dec. 128)
1;2x7 cavo piatto;PinHeader_2x07_P2.54mm_Vertical;J3;stesso ordine di J2 su cue.py (FILI)
1;2x3 cavo piatto;PinHeader_2x03_P2.54mm_Vertical;J4;stesso ordine di J3 su cue.py (CUFFIE)
1;10k lin, scatto al centro;Potentiometer_Alps_RK09L_Double_Vertical;RV1;BLEND: antiorario = cue, centro = 50/50 (-6 dB per parte), orario = master; manopola BLEND, pot di classe 14 mm, cappuccio 15.0 mm
1;10k log;Potentiometer_Alps_RK09L_Double_Vertical;RV2;LEVEL: antiorario = silenzio vero (cursore a massa); manopola LEVEL, pot di classe 14 mm, cappuccio 12.0 mm
